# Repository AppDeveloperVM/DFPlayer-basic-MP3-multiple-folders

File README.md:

# DFPlayer basic MP3 multiple folders
 DFPlayer project with all the basics needed for an MP3

Main features
- Power On/ Power Off
- Play song / Play next song
- Pause / Resume
- Change Songs folder to play

DFPlayer Things to be aware of:

- It is important to have a DFPlayer DFRobots brand, the chinese copies dont usually work as they should.
  For $5.90 you can purchase one. (https://www.dfrobot.com/product-1121.html)
- The module operating Voltage is 3.3V/5V

How to: 

- Play song from Folder : SONGS _outside_ mp3 folder should have the name format nnn.mp3,where the n is a number. 
In case of a number with 2 or less digits, should come with zeros to the left, like 2 being 002.mp3 or 20 being 020.mp3.

- The FOLDER name should be between 1 and 99, also followed by a zero to the left in case of a 1digit number.
Use the funtion PlayFolder(folder number, file number) to play a sound from a folder.

- Play Advertisement : If you want a sound to play like and advertisement, interrumping another sounds or songs, and playing over them, you must place it inside the folder 'advert',
in the root directory. That one can be called using PlayAdvertidement(song number) function.
The thing is, using the function means it can be called WHILE a sound is already being played, you cant call it if no sound is playing.

A basic dfplayer project can look like this :
(from https://www.dfrobot.com/blog-1462.html )

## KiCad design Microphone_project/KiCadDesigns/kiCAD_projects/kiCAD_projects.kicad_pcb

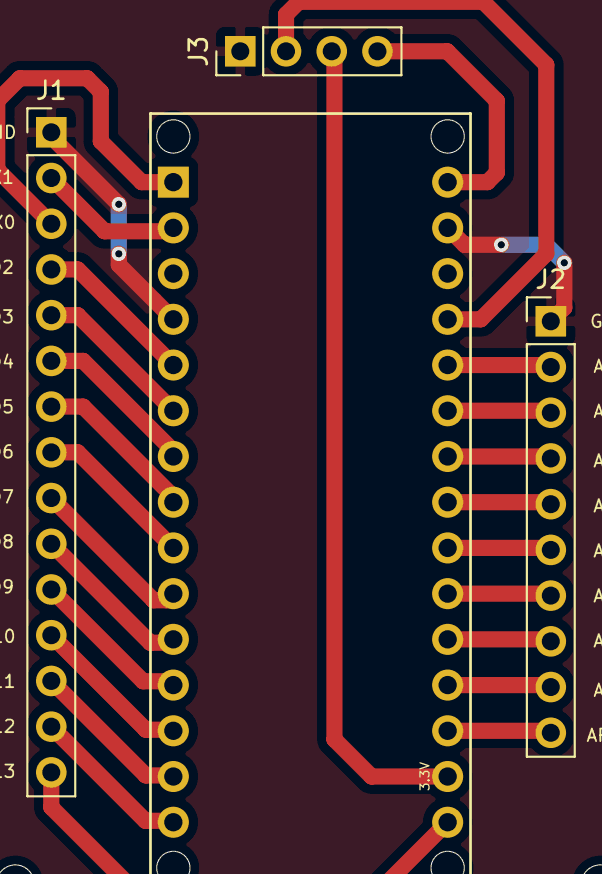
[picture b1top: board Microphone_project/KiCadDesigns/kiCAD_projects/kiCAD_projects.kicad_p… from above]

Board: 2 copper layers, 8 parts (0 on the bottom side), 27 nets.

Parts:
A1: Arduino_Nano_v3.x; Arduino_Nano_Socket
H1, H2, H3, H4: MountingHole; MountingHole_2.1mm
J1: Conn_01x15_Male; PinHeader_1x15_P2.54mm_Vertical
J2: Conn_01x10_Male; PinHeader_1x10_P2.54mm_Vertical
J3: Conn_01x04_Male; PinHeader_1x04_P2.54mm_Vertical

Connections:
GND: J1.1, J2.1, J3.1
unnamed: A1.3V3, J3.3
unnamed: A1.5V, J3.2
unnamed: A1.A0, J2.9
unnamed: A1.A1, J2.8
unnamed: A1.A2, J2.7
unnamed: A1.A3, J2.6
unnamed: A1.A4, J2.5
unnamed: A1.A5, J2.4
unnamed: A1.A6, J2.3
unnamed: A1.A7, J2.2
unnamed: A1.AREF, J2.10
unnamed: A1.D0, J1.2
unnamed: A1.D1, J1.3
unnamed: A1.D2, J1.4
unnamed: A1.D3, J1.5
unnamed: A1.D4, J1.6
unnamed: A1.D5, J1.7
unnamed: A1.D6, J1.8
unnamed: A1.D7, J1.9
unnamed: A1.D8, J1.10
unnamed: A1.D9, J1.11
unnamed: A1.D10, J1.12
unnamed: A1.D11, J1.13
unnamed: A1.D12, J1.14
unnamed: A1.D13, J1.15
unnamed: A1.VIN, J3.4

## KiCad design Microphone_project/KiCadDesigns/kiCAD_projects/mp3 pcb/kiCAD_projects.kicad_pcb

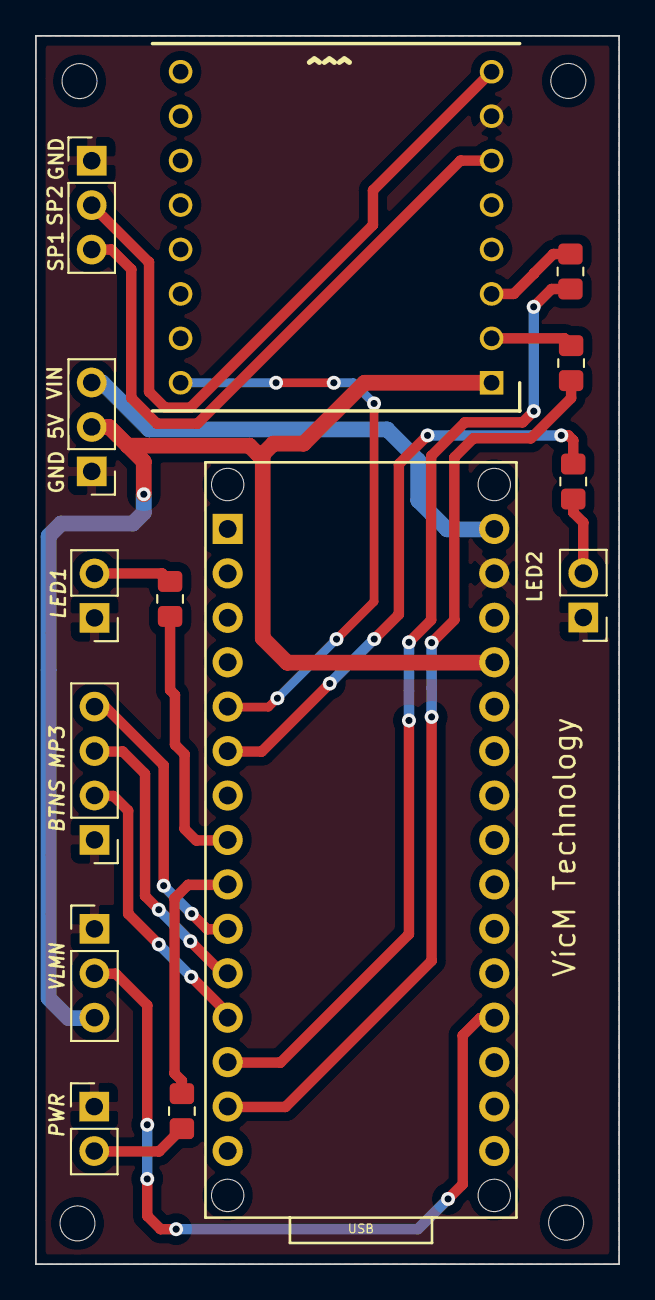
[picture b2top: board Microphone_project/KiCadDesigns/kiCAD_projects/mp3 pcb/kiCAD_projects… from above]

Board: 2 copper layers, 33.3 x 70.2 mm, 18 parts (0 on the bottom side), 20 nets.

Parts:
A1: Arduino_Nano_v3.x; Arduino_Nano_Socket
H1, H2, H3, H4: MountingHole; MountingHole_2mm
J1: PinHeader_1x02_P2.54mm_Vertical
J2, J6: Conn_01x03_Female; PinHeader_1x03_P2.54mm_Vertical
J3, J5: Conn_01x02_Female; PinHeader_1x02_P2.54mm_Vertical
J4: Conn_01x04_Female; PinHeader_1x04_P2.54mm_Vertical
J7: Conn_01x03_Male; PinHeader_1x03_P2.54mm_Vertical
R1, R2: R; R_0805_2012Metric_Pad1.20x1.40mm_HandSolder
R3, R4, R5: R_Small; R_0805_2012Metric_Pad1.20x1.40mm_HandSolder
U1: DFR0299; DIPS1778W50P254L2100H170Q16N

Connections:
GND: A1.GND2, J1.1, J2.1, J3.1, J4.1, J5.1, J6.1, J7.1, U1.7
unnamed: A1.5V, J6.3, J7.2, U1.1
unnamed: A1.A0, J6.2
unnamed: A1.D2, U1.16
unnamed: A1.D3, R4.2
unnamed: A1.D5, R3.2
unnamed: A1.D6, R5.1
unnamed: A1.D7, J4.4
unnamed: A1.D8, J4.3
unnamed: A1.D9, J4.2
unnamed: A1.D10, R1.1
unnamed: A1.D11, R2.1
unnamed: A1.VIN, J7.3
unnamed: J1.2, R5.2
unnamed: J2.2, U1.8
unnamed: J2.3, U1.6
unnamed: J3.2, R3.1
unnamed: J5.2, R4.1
unnamed: R1.2, U1.3
unnamed: R2.2, U1.2

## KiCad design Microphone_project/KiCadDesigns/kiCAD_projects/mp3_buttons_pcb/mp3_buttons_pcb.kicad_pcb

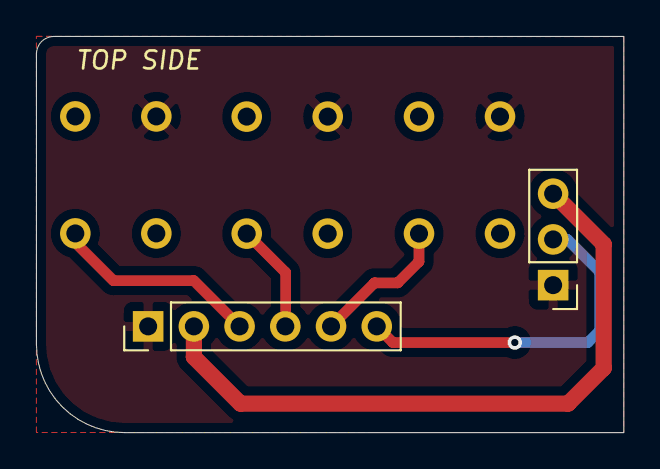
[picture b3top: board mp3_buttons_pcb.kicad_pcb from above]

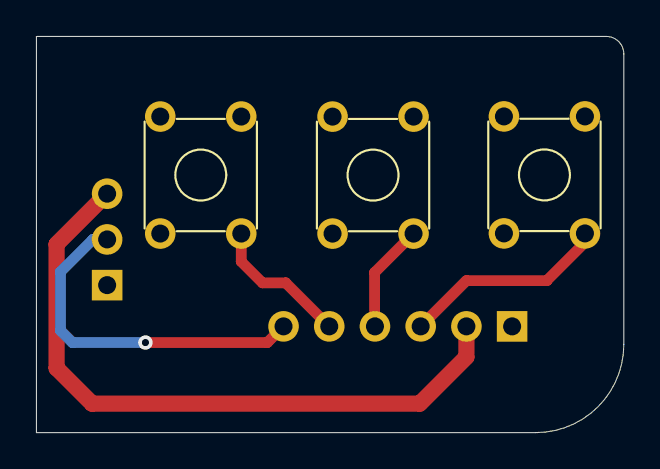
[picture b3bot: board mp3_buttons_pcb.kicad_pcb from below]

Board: 2 copper layers, 32.6 x 22.0 mm, 5 parts (3 on the bottom side), 6 nets.

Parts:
J1: Conn_01x06_Female; PinHeader_1x06_P2.54mm_Vertical
J2: Conn_01x03_Male; PinHeader_1x03_P2.54mm_Vertical
SW1, SW2, SW3: SW_DIP_x02; SW_TH_Tactile_Omron_B3F-10xx

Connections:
+5V: J1.2, J2.3
GND: J1.1, J2.1, SW1.2, SW2.2, SW3.2
unnamed: J1.3, SW1.3
unnamed: J1.4, SW2.3
unnamed: J1.5, SW3.3
unnamed: J1.6, J2.2

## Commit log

2021-05-13 add microphone_project.ino
    arduino file
2021-06-09 Improved code - changed button pins, init sound not resumable
2021-06-12 Fixed errors, Improved readability
2021-06-12 Visual Minor changes
2021-07-30 Version 2 - Upgrades
    - BUSY Pin in use (isPlaying)
    - Resume / Pause button initiates first song in some cases
    ( initSound = true & folderchange = true )
2021-08-05 Use of Libraries , Use of Potentiometer
    Libraries :
    - ezButton
    Potentiometer in A0 pin receveing volume data
2021-08-05 Commentary
2021-08-06 Change Volume with Potentiometer - Added !
    - 'A0' Pin used by Potentiometer
    - Volume can be changed while music is playing
2021-08-14 Power switch button doesnt like ezButton lib
    use of old method for power button
2021-08-15 Improved potentiometer reading
2021-08-17 POWER button probs fixed / error checker added
2022-03-13 Added KiCad designs and assets
